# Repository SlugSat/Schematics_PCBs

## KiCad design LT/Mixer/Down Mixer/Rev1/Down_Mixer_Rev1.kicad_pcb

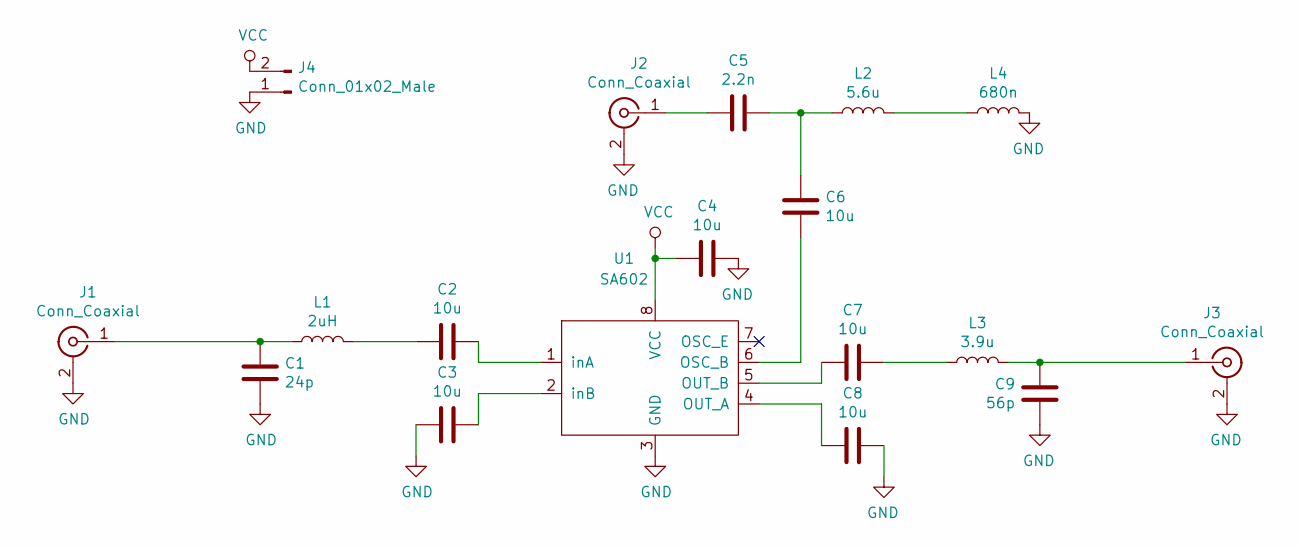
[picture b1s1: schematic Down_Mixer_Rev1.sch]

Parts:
C1: 24p; C_0805_2012Metric_Pad1.15x1.40mm_HandSolder
C2, C3, C4, C6, C7, C8: 10u; C_0805_2012Metric_Pad1.15x1.40mm_HandSolder
C5: 2.2n; C_0805_2012Metric_Pad1.15x1.40mm_HandSolder
C9: 56p; C_0805_2012Metric_Pad1.15x1.40mm_HandSolder
J1, J2, J3: Conn_Coaxial; SMA_Amphenol_132289_EdgeMount
J4: Conn_01x02_Male; PinHeader_1x02_P2.54mm_Vertical
L1: 2uH; L_0805_2012Metric_Pad1.15x1.40mm_HandSolder
L2: 5.6u; L_0805_2012Metric_Pad1.15x1.40mm_HandSolder
L3: 3.9u; L_0805_2012Metric_Pad1.15x1.40mm_HandSolder
L4: 680n; L_0805_2012Metric_Pad1.15x1.40mm_HandSolder
U1: SA602; SO-8_3.9x4.9mm_P1.27mm

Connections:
GND: C1.2, C3.2, C4.2, C8.2, C9.2, J1.2 (Ext), J2.2 (Ext), J3.2 (Ext), J4.1, L4.2, U1.3 (GND)
unnamed: C1.1, J1.1 (In), L1.1
unnamed: C2.1, U1.1 (inA)
unnamed: C2.2, L1.2
unnamed: C3.1, U1.2 (inB)
unnamed: C5.1, J2.1 (In)
unnamed: C5.2, C6.1, L2.1
unnamed: C6.2, U1.6 (OSC_B)
unnamed: C7.1, U1.5 (OUT_B)
unnamed: C7.2, L3.2
unnamed: C8.1, U1.4 (OUT_A)
unnamed: C9.1, J3.1 (In), L3.1
unnamed: L2.2, L4.1
VCC: C4.1, J4.2, U1.8 (VCC)

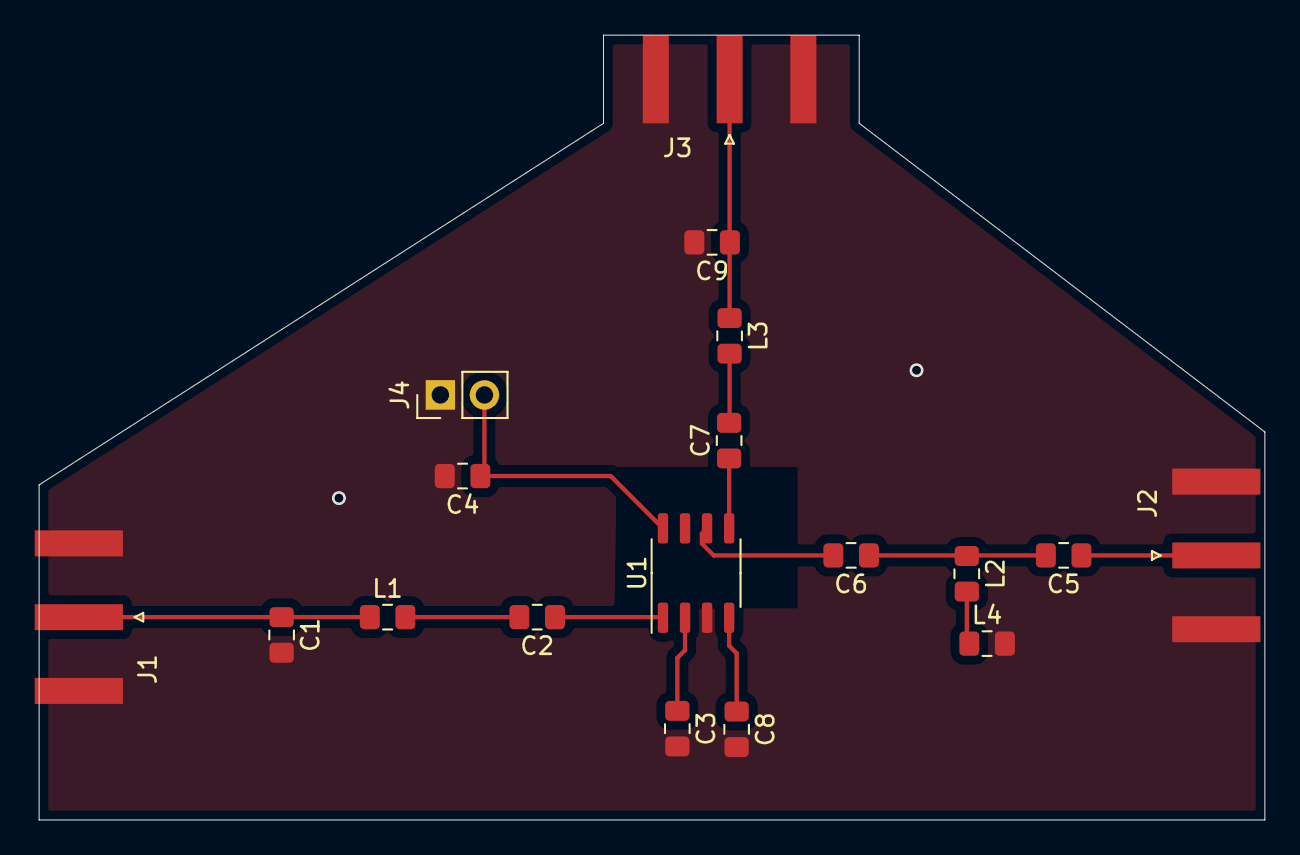
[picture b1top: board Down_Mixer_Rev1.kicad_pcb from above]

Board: 2 copper layers, 70.6 x 45.2 mm, 18 parts (0 on the bottom side), 14 nets.

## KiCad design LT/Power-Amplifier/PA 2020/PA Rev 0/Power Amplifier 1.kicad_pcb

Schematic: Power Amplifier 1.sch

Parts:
C0: 10 uF; PinHeader_1x02_P2.54mm_Vertical
C1: 10 nF; C_0805_2012Metric_Pad1.15x1.40mm_HandSolder
C2: 22 nF; C_0805_2012Metric_Pad1.15x1.40mm_HandSolder
CB1, CB2: 100 nF; C_0805_2012Metric_Pad1.15x1.40mm_HandSolder
D0: 1N4001; D_DO-35_SOD27_P12.70mm_Horizontal
J0: Power; PinHeader_1x02_P2.54mm_Vertical
J1: Signal In; PinHeader_1x02_P2.54mm_Vertical
J2: SMA Connector; SMA_Molex_73251-1153_EdgeMount_Horizontal
Q1: NPN; PinHeader_1x03_P2.54mm_Vertical
Q2: PNP; PinHeader_1x03_P2.54mm_Vertical
R1: 4.7 kOhms; R_0805_2012Metric_Pad1.15x1.40mm_HandSolder
R2: 1 kOhms; R_0805_2012Metric_Pad1.15x1.40mm_HandSolder
R3: 47 Ohms; R_0805_2012Metric_Pad1.15x1.40mm_HandSolder
T1: 8:4T Xformer; XFormer84Tapped
T2: 8T:4 XFormer; XFormer8Tapped4
U0: L7815; TO-220-3_Vertical

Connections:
GND: C2.2, CB1.2, CB2.2, J0.2, J1.2, J2.2, R2.2, R3.2, T1.2 (AB), T2.4 (S1), U0.2 (GND)
unnamed: C0.1, C1.1, CB2.1, R1.1, T2.2 (PM), U0.3 (OUT)
unnamed: C0.2, C1.2, J1.1, T1.1 (AA)
unnamed: C2.1, R1.2, R2.1, T1.4 (SC)
unnamed: CB1.1, D0.1 (K), U0.1 (IN)
unnamed: D0.2 (A), J0.1
unnamed: J2.1, T2.5 (S2)
unnamed: Q1.1, Q2.1, R3.1
unnamed: Q1.2, T1.5 (SB)
unnamed: Q1.3, T2.1 (PR1)
unnamed: Q2.2, T1.3 (SA)
unnamed: Q2.3, T2.3 (PR2)

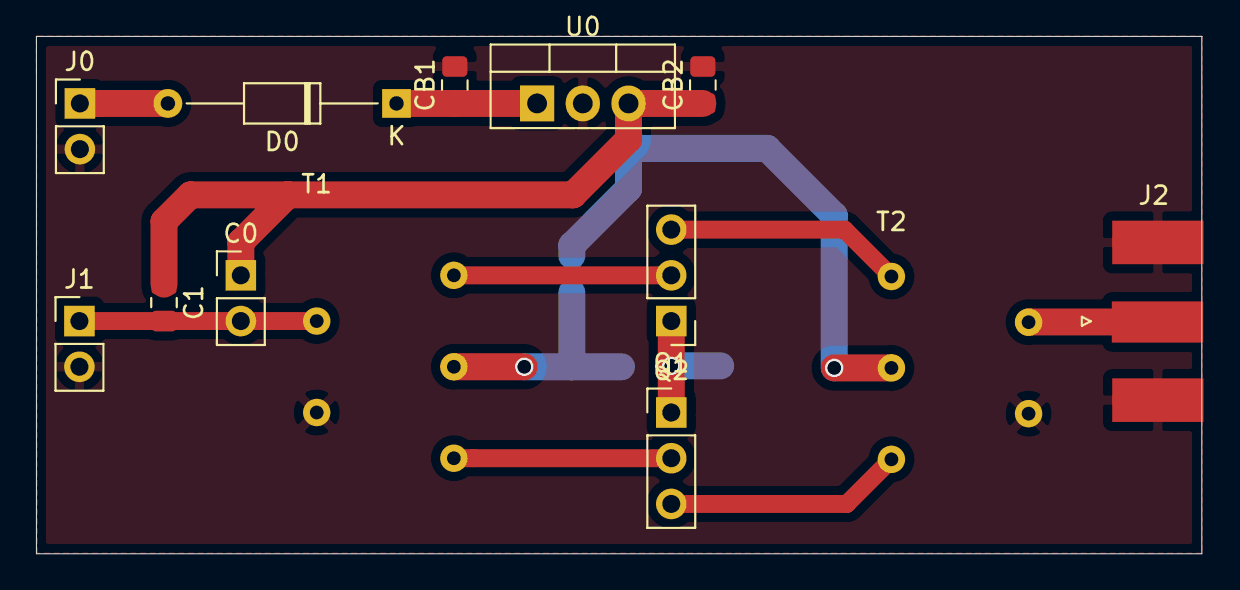
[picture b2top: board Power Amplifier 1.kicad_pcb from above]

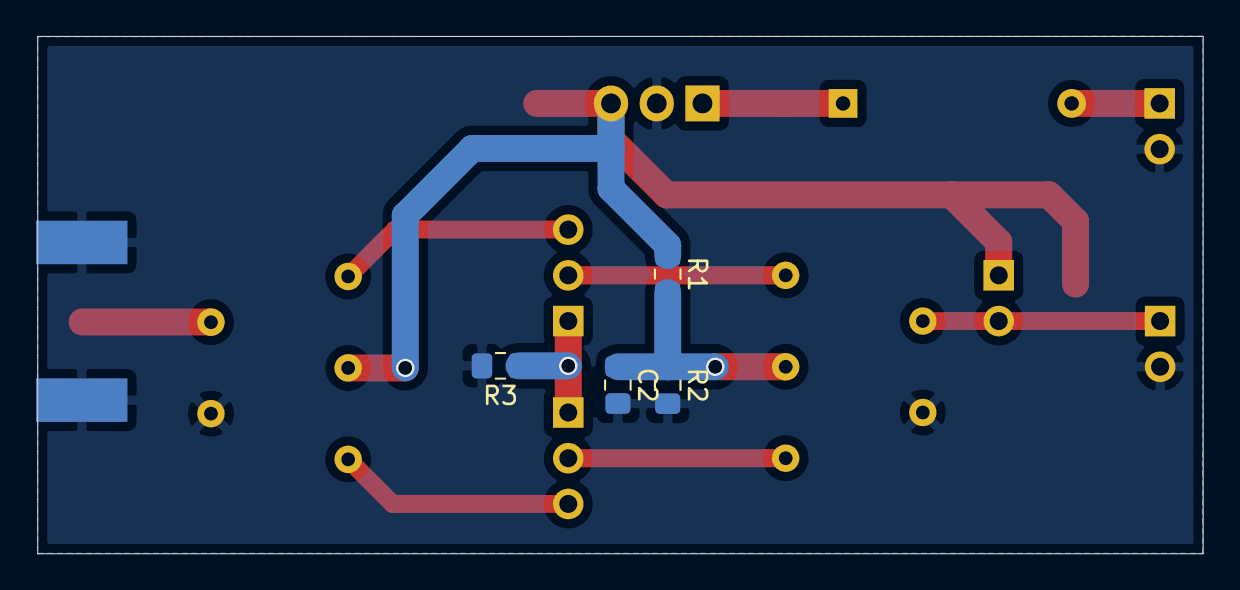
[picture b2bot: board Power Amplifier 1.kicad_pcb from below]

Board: 2 copper layers, 64.7 x 28.7 mm, 17 parts (4 on the bottom side), 12 nets.

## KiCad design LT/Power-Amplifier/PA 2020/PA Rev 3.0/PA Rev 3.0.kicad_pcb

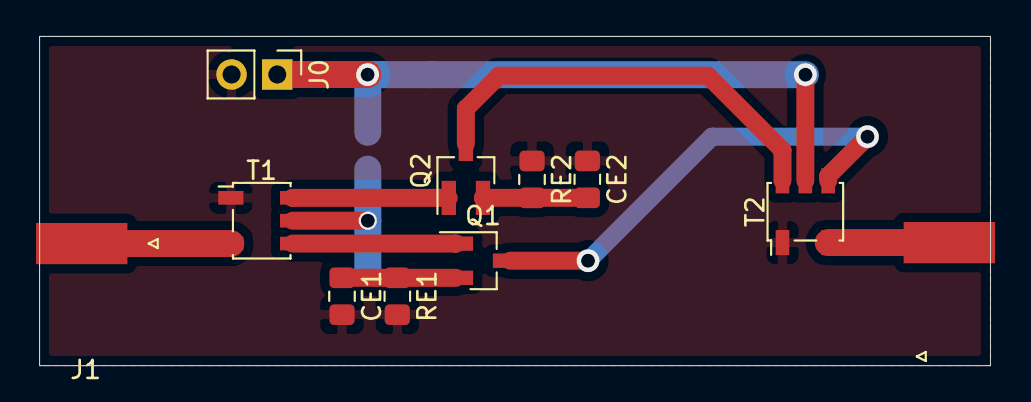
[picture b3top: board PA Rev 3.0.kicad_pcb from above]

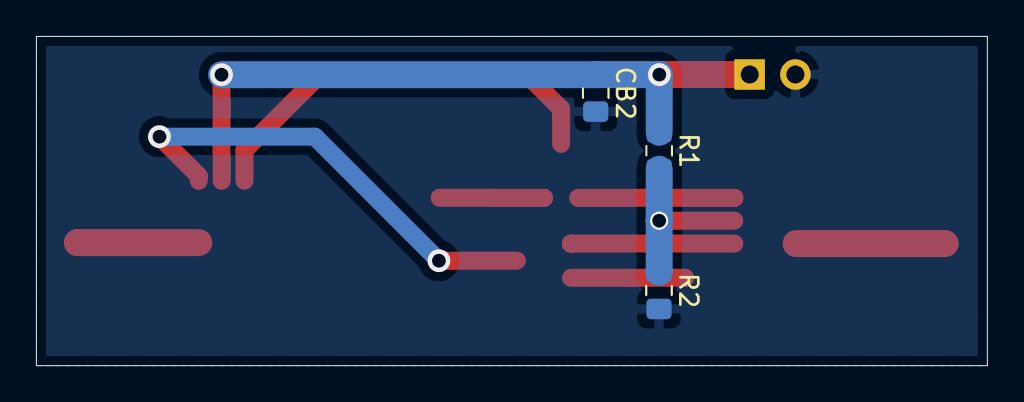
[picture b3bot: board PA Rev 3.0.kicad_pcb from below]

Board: 2 copper layers, 52.8 x 18.3 mm, 14 parts (3 on the bottom side), 11 nets.

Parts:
CB2: 100 nF; C_0805_2012Metric_Pad1.15x1.40mm_HandSolder
CE1, CE2: 100 nF; C_0805_2012Metric_Pad1.15x1.40mm_HandSolder
J0: Power; PinHeader_1x02_P2.54mm_Vertical
J1: RF IN; SMA_Molex_73251-1153_EdgeMount_Horizontal
J2: RF OUT; SMA_Molex_73251-1153_EdgeMount_Horizontal
Q1: NPN; SOT-23_Handsoldering
Q2: PNP; SOT-23_Handsoldering
R1: 4.7k Ohms; R_0805_2012Metric_Pad1.15x1.40mm_HandSolder
R2: 3.3k Ohms; R_0805_2012Metric_Pad1.15x1.40mm_HandSolder
RE1, RE2: 47 Ohms; R_0805_2012Metric_Pad1.15x1.40mm_HandSolder
T1, T2: RF_XFormer; Transformer_MACOM_SM-22

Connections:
GND: CB2.2, CE1.2, CE2.1, J0.2, R2.2, RE1.2, RE2.1, T1.1, T2.1
unnamed: CB2.1, J0.1, T2.4
unnamed: CE1.1, Q1.2, RE1.1
unnamed: CE2.2, Q2.2, RE2.2
unnamed: J1.1, T1.2
unnamed: J2.1, T2.2
unnamed: Q1.1, T1.3
unnamed: Q1.3, T2.3
unnamed: Q2.1, T1.5
unnamed: Q2.3, T2.5
unnamed: R1.2, R2.1, T1.4

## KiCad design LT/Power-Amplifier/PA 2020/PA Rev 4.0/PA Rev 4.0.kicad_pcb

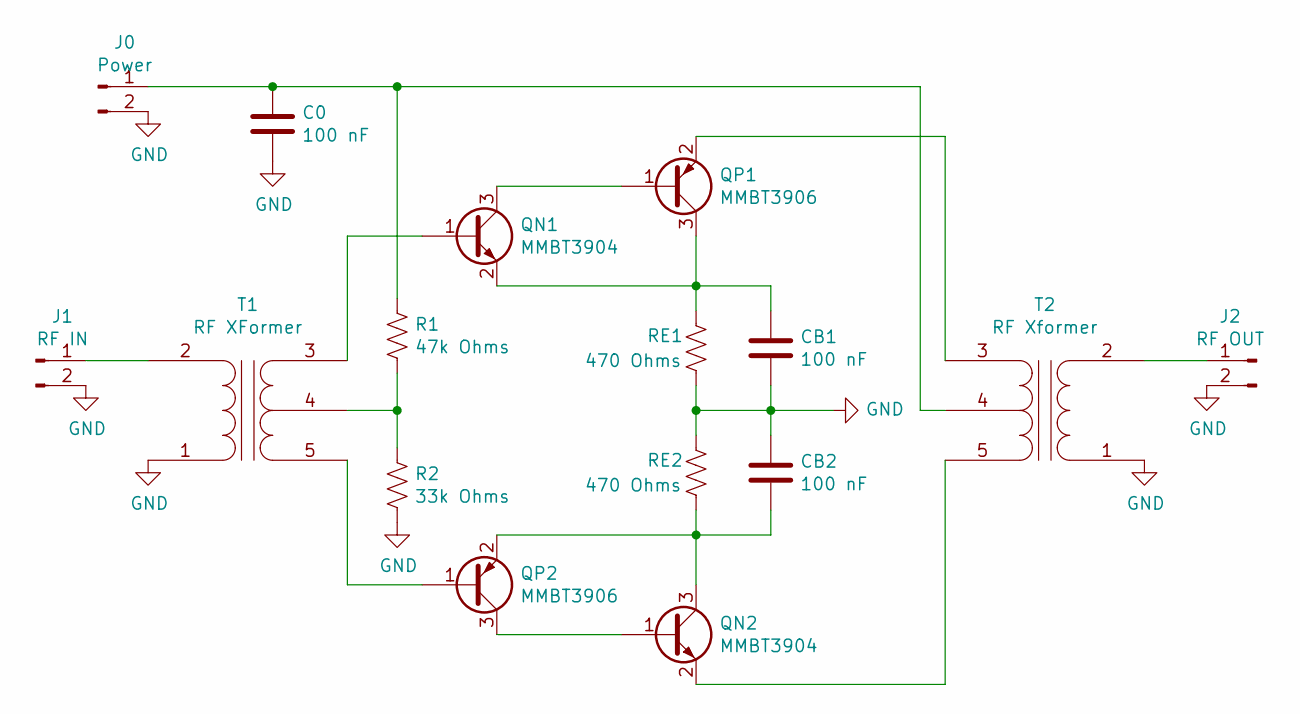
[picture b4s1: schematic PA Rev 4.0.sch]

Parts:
C0: 100 nF; C_0805_2012Metric_Pad1.15x1.40mm_HandSolder
CB1, CB2: 100 nF; C_0805_2012Metric_Pad1.15x1.40mm_HandSolder
J0: Power; PinHeader_1x02_P2.54mm_Vertical
J1: RF IN; SMAConnector
J2: RF OUT; SMAConnector
QN1, QN2: MMBT3904; SOT-23_Handsoldering
QP1, QP2: MMBT3906; SOT-23_Handsoldering
R1: 47k Ohms; R_0805_2012Metric_Pad1.15x1.40mm_HandSolder
R2: 33k Ohms; R_0805_2012Metric_Pad1.15x1.40mm_HandSolder
RE1, RE2: 470 Ohms; R_0805_2012Metric_Pad1.15x1.40mm_HandSolder
T1: RF XFormer; Transformer_MACOM_SM-22
T2: RF Xformer; Transformer_MACOM_SM-22

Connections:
GND: C0.2, CB1.2, CB2.1, J0.2, J1.2, J2.2, R2.2, RE1.2, RE2.1, T1.1 (AA), T2.1 (AA)
unnamed: C0.1, J0.1, R1.1, T2.4 (SC)
unnamed: CB1.1, QN1.2 (E), QP1.3 (C), RE1.1
unnamed: CB2.2, QN2.3 (C), QP2.2 (E), RE2.2
unnamed: J1.1, T1.2 (AB)
unnamed: J2.1, T2.2 (AB)
unnamed: QN1.1 (B), T1.3 (SA)
unnamed: QN1.3 (C), QP1.1 (B)
unnamed: QN2.1 (B), QP2.3 (C)
unnamed: QN2.2 (E), T2.5 (SB)
unnamed: QP1.2 (E), T2.3 (SA)
unnamed: QP2.1 (B), T1.5 (SB)
unnamed: R1.2, R2.1, T1.4 (SC)

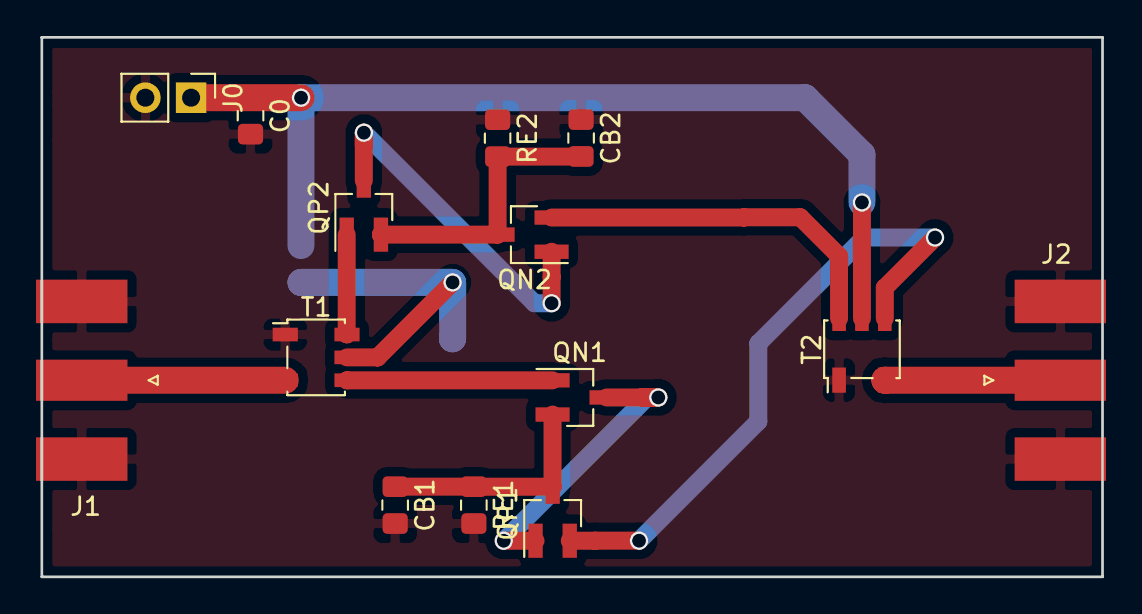
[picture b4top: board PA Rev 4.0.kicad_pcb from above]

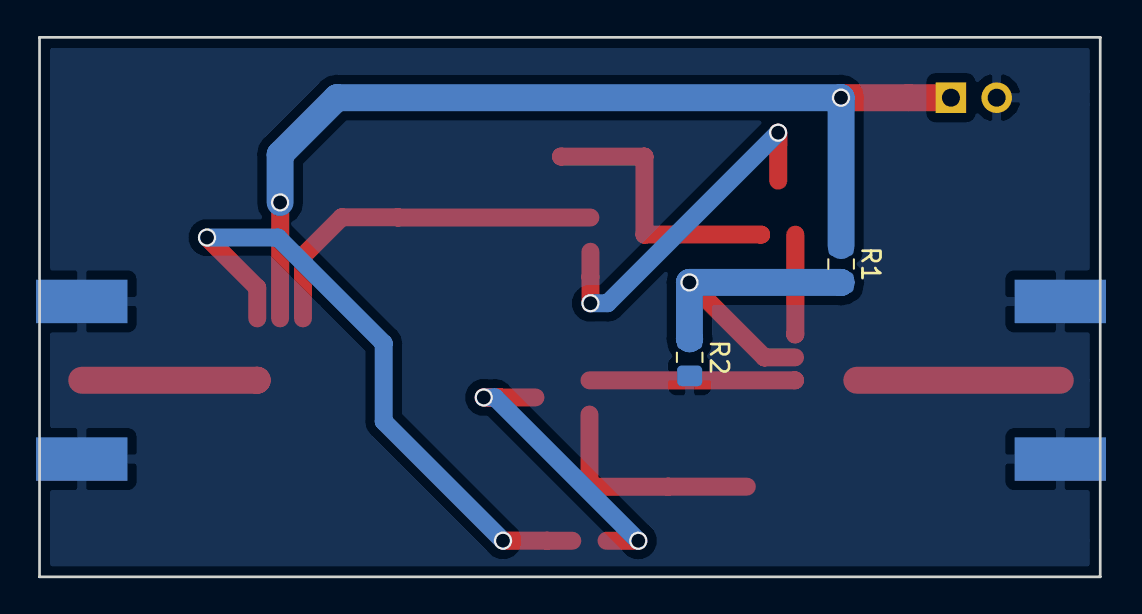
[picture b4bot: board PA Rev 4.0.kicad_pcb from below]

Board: 2 copper layers, 58.9 x 30.0 mm, 16 parts (2 on the bottom side), 13 nets.

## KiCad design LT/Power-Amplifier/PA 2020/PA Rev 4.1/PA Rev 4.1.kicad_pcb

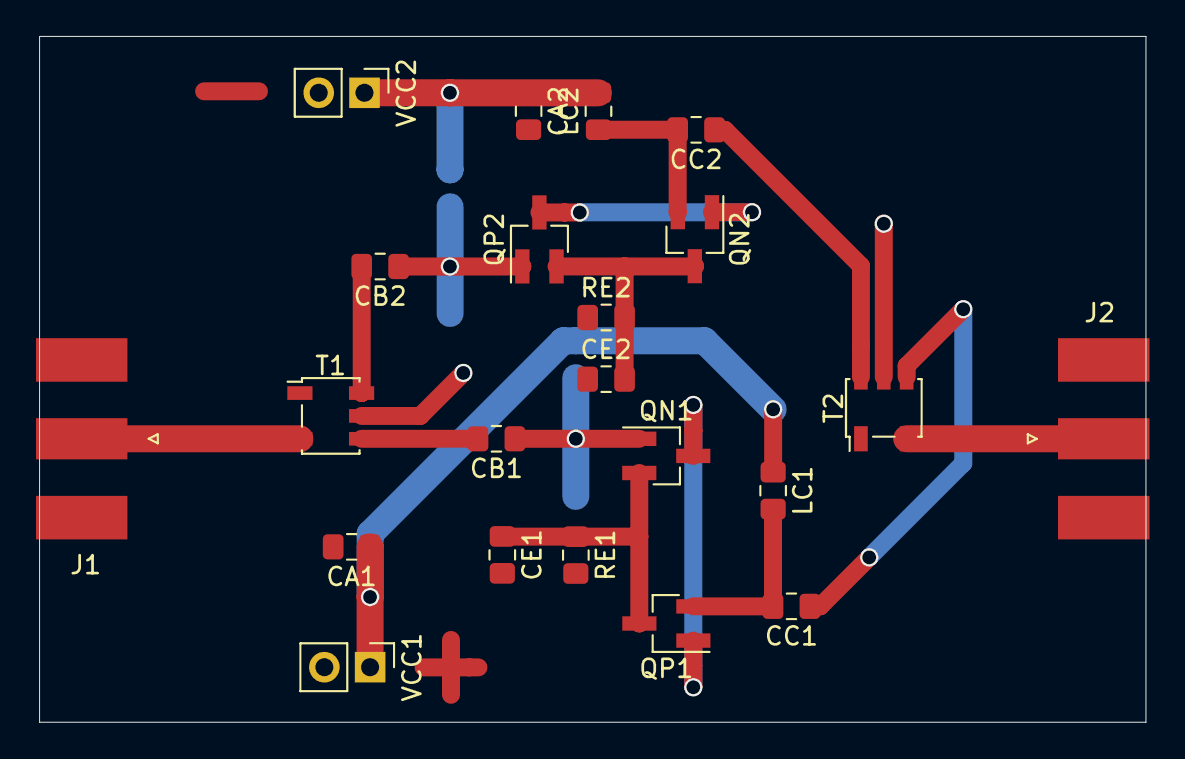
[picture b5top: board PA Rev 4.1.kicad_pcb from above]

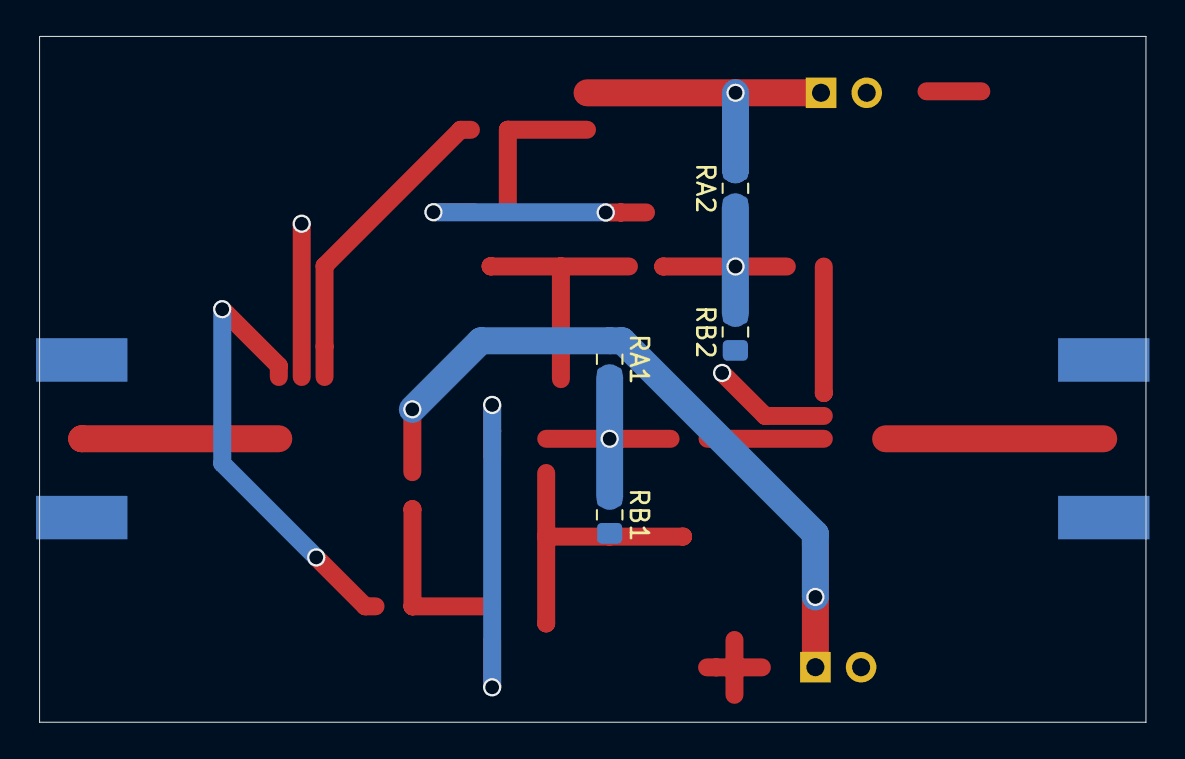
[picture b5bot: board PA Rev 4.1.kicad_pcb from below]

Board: 2 copper layers, 61.5 x 38.1 mm, 26 parts (4 on the bottom side), 17 nets.

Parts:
CA1, CA2: 100 nF; C_0805_2012Metric_Pad1.15x1.40mm_HandSolder
CB1, CB2: 47 nF; C_0805_2012Metric_Pad1.15x1.40mm_HandSolder
CC1, CC2: 29.3 pF; C_0805_2012Metric_Pad1.15x1.40mm_HandSolder
CE1, CE2: 100 nF; C_0805_2012Metric_Pad1.15x1.40mm_HandSolder
J1: RF In; SMA_Molex_73251-1153_EdgeMount_Horizontal
J2: RF Out; SMA_Molex_73251-1153_EdgeMount_Horizontal
LC1, LC2: 1 uH; L_0805_2012Metric_Pad1.15x1.40mm_HandSolder
QN1, QN2: MMBT3904; SOT-23_Handsoldering
QP1, QP2: MMBT3906; SOT-23_Handsoldering
RA1, RA2: 47k Ohms; R_0805_2012Metric_Pad1.15x1.40mm_HandSolder
RB1, RB2: 33k Ohms; R_0805_2012Metric_Pad1.15x1.40mm_HandSolder
RE1, RE2: 470 Ohms; R_0805_2012Metric_Pad1.15x1.40mm_HandSolder
T1, T2: RF XFormer; Transformer_MACOM_SM-22
VCC1, VCC2: Power; PinHeader_1x02_P2.54mm_Vertical

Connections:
GND: CA1.2, CA2.2, CE1.2, CE2.1, J1.2, J2.2, RB1.2, RB2.1, RE1.2, RE2.1, T1.1, T1.4, T2.1, T2.4, VCC1.2, VCC2.2
unnamed: CA1.1, LC1.1, RA1.1, VCC1.1
unnamed: CA2.1, LC2.2, RA2.2, VCC2.1
unnamed: CB1.1, QN1.1, RA1.2, RB1.1
unnamed: CB1.2, T1.3
unnamed: CB2.1, QP2.1, RA2.1, RB2.2
unnamed: CB2.2, T1.5
unnamed: CC1.1, T2.3
unnamed: CC1.2, LC1.2, QP1.2
unnamed: CC2.1, T2.5
unnamed: CC2.2, LC2.1, QN2.2
unnamed: CE1.1, QN1.2, QP1.3, RE1.1
unnamed: CE2.2, QN2.3, QP2.2, RE2.2
unnamed: J1.1, T1.2
unnamed: J2.1, T2.2
unnamed: QN1.3, QP1.1
unnamed: QN2.1, QP2.3

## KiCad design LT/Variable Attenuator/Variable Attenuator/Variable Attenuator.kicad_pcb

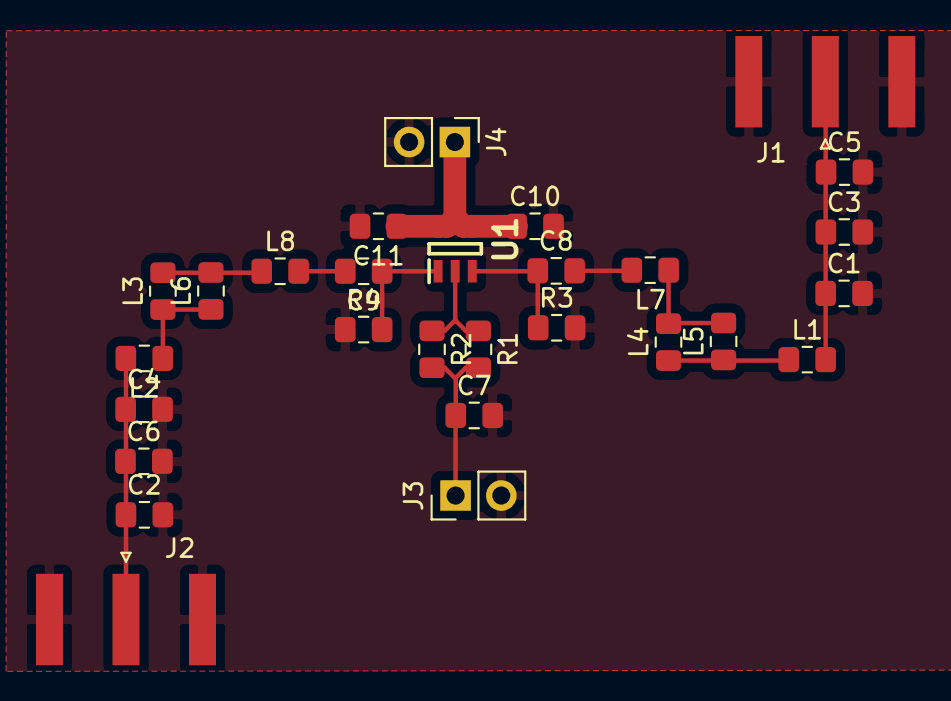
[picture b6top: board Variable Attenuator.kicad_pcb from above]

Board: 2 copper layers, 28 parts (0 on the bottom side), 14 nets.

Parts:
C1, C2: 220pF; C_0805_2012Metric_Pad1.15x1.40mm_HandSolder
C3, C4: 22pF; C_0805_2012Metric_Pad1.15x1.40mm_HandSolder
C5, C6: 330pF; C_0805_2012Metric_Pad1.15x1.40mm_HandSolder
C7: 10nH; C_0805_2012Metric_Pad1.15x1.40mm_HandSolder
C8, C9, C10, C11: 10nF; C_0805_2012Metric_Pad1.15x1.40mm_HandSolder
J1, J2: Conn_Coaxial; SMA_Amphenol_132289_EdgeMount
J3, J4: Conn_01x02_Male; PinHeader_1x02_P2.54mm_Vertical
L1, L2: 3.9nH; L_0805_2012Metric_Pad1.15x1.40mm_HandSolder
L3, L4, L5, L6: 47nH; L_0805_2012Metric_Pad1.15x1.40mm_HandSolder
L7, L8: 150nH; L_0805_2012Metric_Pad1.15x1.40mm_HandSolder
R1, R2: 120; R_0805_2012Metric_Pad1.15x1.40mm_HandSolder
R3, R4: 330; R_0805_2012Metric_Pad1.15x1.40mm_HandSolder
U1: BAP64Q

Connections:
+5V: C10.1, C11.1, J4.1, U1.4, U1.5
GND: C1.2, C2.2, C3.2, C4.2, C5.2, C6.2, C7.2, C10.2, C11.2, J1.2, J2.2, J3.2, J4.2, R3.2, R4.1
unnamed: C1.1, C3.1, C5.1, J1.1, L1.2
unnamed: C2.1, C4.1, C6.1, J2.1, L2.2
unnamed: C7.1, J3.1, R1.2, R2.2
unnamed: C8.1, R3.1, U1.3
unnamed: C8.2, L7.2
unnamed: C9.1, R4.2, U1.1
unnamed: C9.2, L8.2
unnamed: L1.1, L4.1, L5.1
unnamed: L2.1, L3.1, L6.1
unnamed: L3.2, L6.2, L8.1
unnamed: L4.2, L5.2, L7.1
unnamed: R1.1, R2.1, U1.2
